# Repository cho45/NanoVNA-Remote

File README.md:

# NanoVNA Wi-Fi connection impl.

## Schematic

 * ./cdc-to-websocket/cdc-to-websocket.svg
 * STM32F401 firmware: https://github.com/cho45/stm32f401-usbserial-host

## Configure Wi-Fi Mode (AP or Station)

IO15 is pulled-up input

- connect to GND: work as station for debug (ID/PASS is set by `idf.py menuconfig`)
- open: work as AP

## Build

require esp-idf https://docs.espressif.com/projects/esp-idf/en/latest/esp32/get-started/index.html#get-started-get-esp-idf

`idf.py build`

build and flash

```
idf.py -p /dev/tty.SLAB_USBtoUART flash monitor
```

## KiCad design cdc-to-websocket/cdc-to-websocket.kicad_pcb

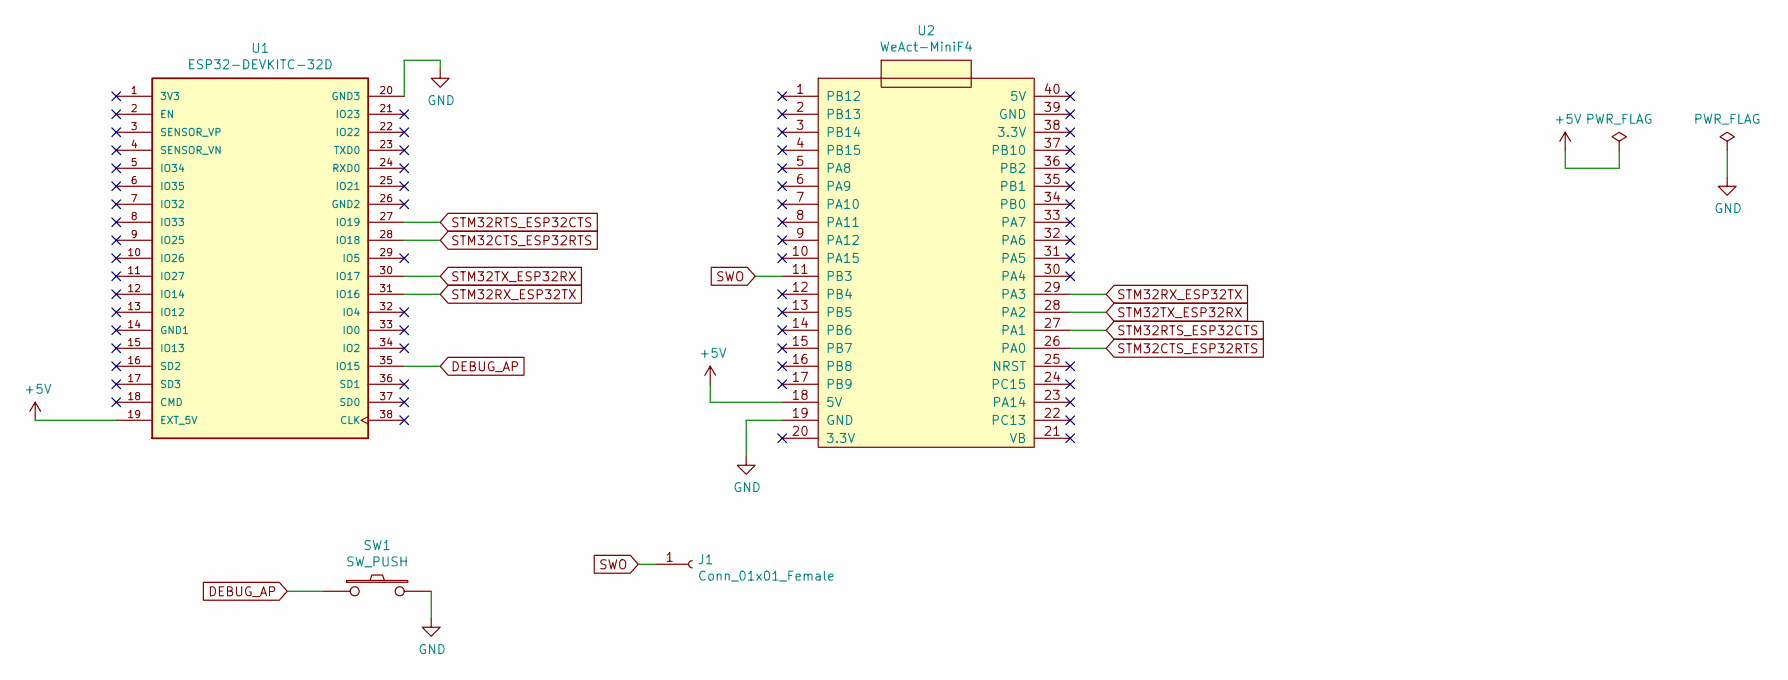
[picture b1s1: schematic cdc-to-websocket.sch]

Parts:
J1: Conn_01x01_Female; SolderWirePad_1x01_Drill0.8mm
SW1: SW_PUSH; SW_Tactile_Straight_KSA0Axx1LFTR
U1: ESP32-DEVKITC-32D; MODULE_ESP32-DEVKITC-32D; PARTREV 4
U2: WeAct-MiniF4

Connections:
+5V: U1.19 (EXT_5V), U2.18 (5V)
DEBUG_AP: SW1.1, U1.35 (IO15)
GND: SW1.2, U1.20 (GND3), U2.19 (GND)
STM32CTS_ESP32RTS: U1.28 (IO18), U2.26 (PA0)
STM32RTS_ESP32CTS: U1.27 (IO19), U2.27 (PA1)
STM32RX_ESP32TX: U1.31 (IO16), U2.29 (PA3)
STM32TX_ESP32RX: U1.30 (IO17), U2.28 (PA2)
SWO: J1.1, U2.11 (PB3)

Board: 2 copper layers, 4 parts (0 on the bottom side), 8 nets, no tracks yet.

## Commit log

2020-11-03 init
2020-11-04 uart
2020-11-04 add sketch
2020-11-04 change log
2020-11-06 work
2020-11-06 update websocket packet size
2020-11-08 copy.sh
2020-11-08 do not store filename/timestamp for gzip-ed files
2020-11-09 some debug info
2020-11-20 add schematics
